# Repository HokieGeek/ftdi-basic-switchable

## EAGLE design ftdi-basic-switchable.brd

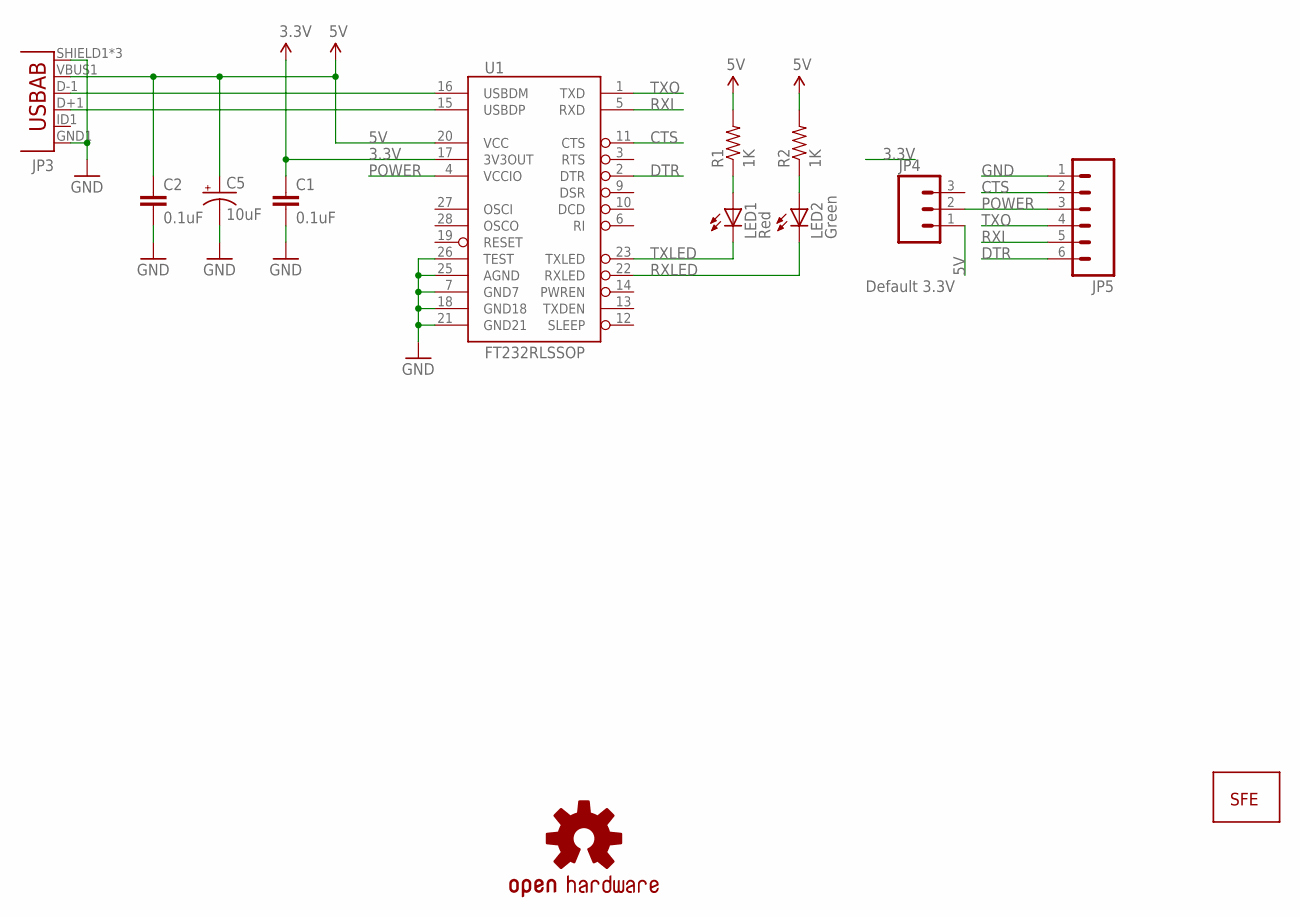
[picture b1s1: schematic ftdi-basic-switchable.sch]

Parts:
C1, C2: 0.1uF; 0402-CAP
C5: 10uF; EIA3216
JP2: LOGO-SFESK; SFE-LOGO-FLAME
JP3: USB-ABCONN-11794; USB-AB-MICRO-SMD_V03
JP4: M03SMD_RA_MALE; 1X03_SMD_RA_MALE
JP5: M06SMD-FEMALE-V2-NOSILK; 1X06-SMD-FEMALE-V2-NOSILK
LED1: Red; LED-0603
LED2: Green; LED-0603
LOGO1: OSHW-LOGOS; OSHW-LOGO-S
R1, R2: 1K; 0402-RES
U1: FT232RLSSOP; SSOP28DB

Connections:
3.3V: C1.1, U1.17 (3V3OUT)
5V: C2.1, C5.A (+), JP3.VBUS1 (VBUS), JP4.1, R1.2, R2.2, U1.20 (VCC)
CTS: JP5.2, U1.11 (CTS)
DTR: JP5.6, U1.2 (DTR)
GND: C1.2, C2.2, C5.C (-), JP3.GND1 (GND), JP3.SHIELD1 (SHIELD), JP3.SHIELD2 (SHIELD), JP3.SHIELD3 (SHIELD), JP5.1, U1.7 (GND7), U1.18 (GND18), U1.21 (GND21), U1.25 (AGND), U1.26 (TEST)
unnamed: LED1.A, R1.1
unnamed: LED2.A, R2.1
POWER: JP4.2, JP5.3, U1.4 (VCCIO)
RXI: JP5.5, U1.5 (RXD)
RXLED: LED2.C, U1.22 (RXLED)
TXLED: LED1.C, U1.23 (TXLED)
TXO: JP5.4, U1.1 (TXD)
USB_D+: JP3.D+1 (D+), U1.15 (USBDP)
USB_D-: JP3.D-1 (D-), U1.16 (USBDM)

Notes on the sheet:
Default 3.3V

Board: 2 copper layers, 13 parts (2 on the bottom side), 14 nets, no tracks yet.

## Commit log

2015-12-01 First attempt at modifying this 4-layer board!
2015-12-01 I dunno

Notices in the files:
parts and their libraries:
SparkFun-Connectors: Licensing: Creative Commons ShareAlike 4.0 International - https://creativecommons.org/licenses/by-sa/4.0
